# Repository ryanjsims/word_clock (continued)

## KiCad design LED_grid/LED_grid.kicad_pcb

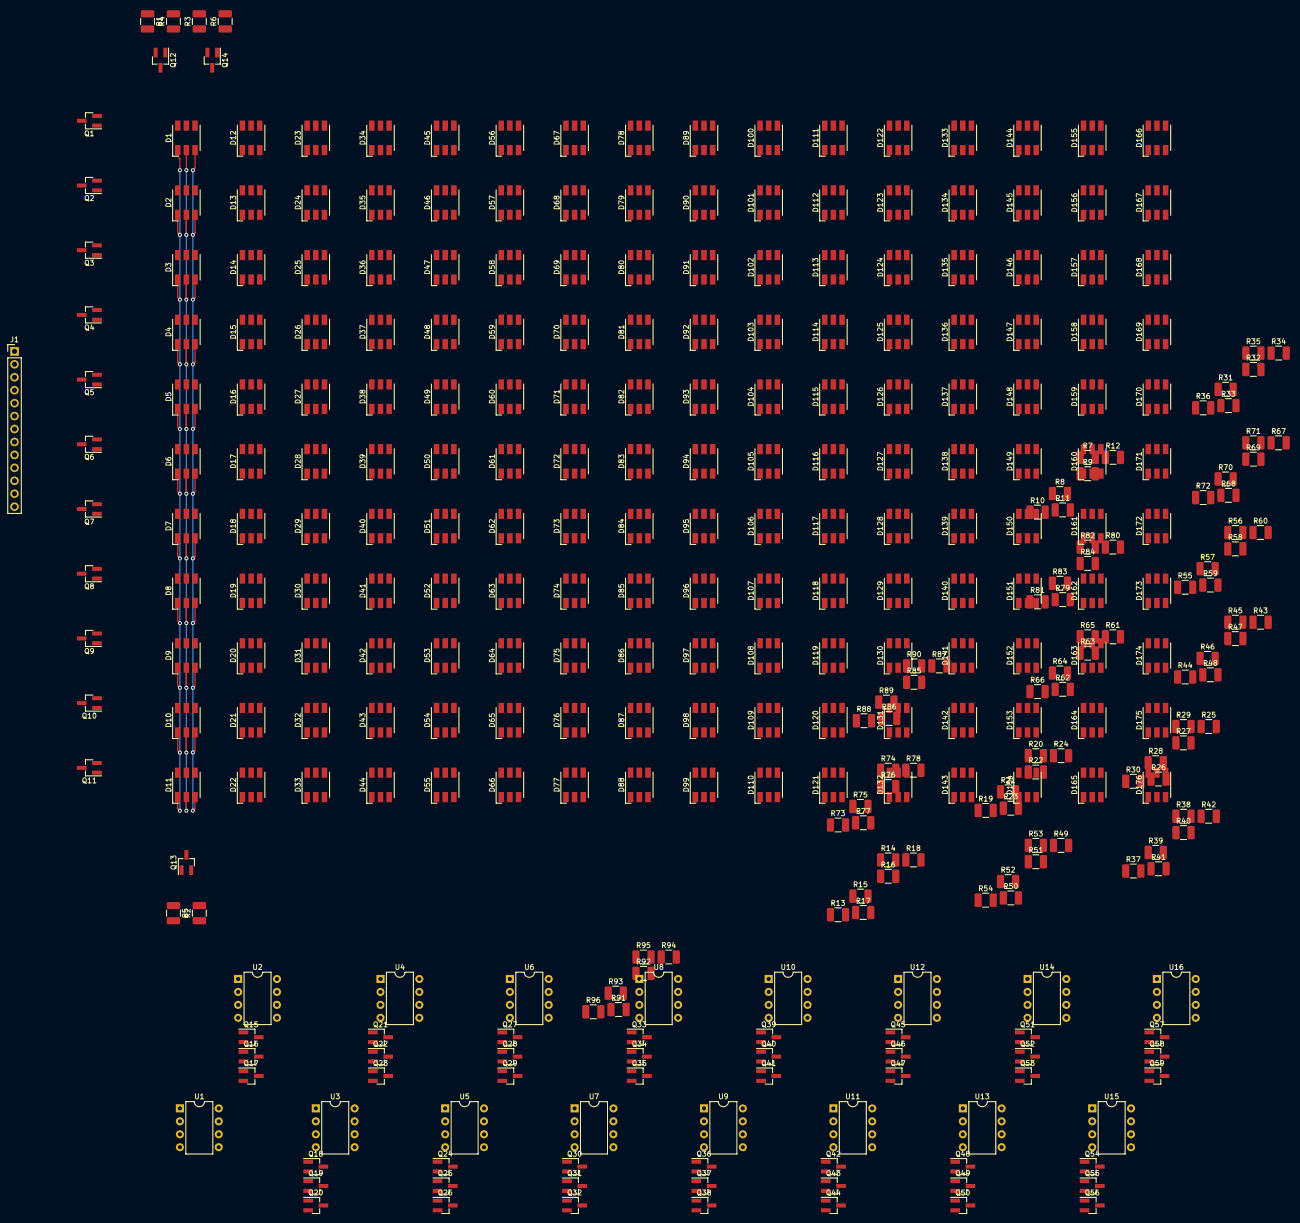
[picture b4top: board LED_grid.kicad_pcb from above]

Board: 2 copper layers, 348 parts (0 on the bottom side), 233 nets.

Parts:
D1, D2, D3, D4, D5, D6, D7, D8, D9, D10, D11, D12, D13, D14, D15, D16, D17, D18, D19, D20, D21, D22, D23, D24, D25, D26, D27, D28, D29, D30, D31, D32, D33, D34, D35, D36, D37, D38, D39, D40, D41, D42, D43, D44, D45, D46, D47, D48, D49, D50, D51, D52, D53, D54, D55, D56, D57, D58, D59, D60, D61, D62, D63, D64, D65, D66, D67, D68, D69, D70, D71, D72, D73, D74, D75, D76, D77, D78, D79, D80, D81, D82, D83, D84, D85, D86, D87, D88, D89, D90, D91, D92, D93, D94, D95, D96, D97, D98, D99, D100, D101, D102, D103, D104, D105, D106, D107, D108, D109, D110, D111, D112, D113, D114, D115, D116, D117, D118, D119, D120, D121, D122, D123, D124, D125, D126, D127, D128, D129, D130, D131, D132, D133, D134, D135, D136, D137, D138, D139, D140, D141, D142, D143, D144, D145, D146, D147, D148, D149, D150, D151, D152, D153, D154, D155, D156, D157, D158, D159, D160, D161, D162, D163, D164, D165, D166, D167, D168, D169, D170, D171, D172, D173, D174, D175, D176: LED_RGB; LED_RGB_5050-6
J1: Conn_01x13; PinHeader_1x13_P2.54mm_Vertical
Q1, Q2, Q3, Q4, Q5, Q6, Q7, Q8, Q9, Q10, Q11: FMMT620CT-ND; SOT-23_Handsoldering
Q12, Q13, Q14, Q15, Q16, Q17, Q18, Q19, Q20, Q21, Q22, Q23, Q24, Q25, Q26, Q27, Q28, Q29, Q30, Q31, Q32, Q33, Q34, Q35, Q36, Q37, Q38, Q39, Q40, Q41, Q42, Q43, Q44, Q45, Q46, Q47, Q48, Q49, Q50, Q51, Q52, Q53, Q54, Q55, Q56, Q57, Q58, Q59: 2N3904; SOT-23_Handsoldering
R1, R2, R3, R7, R8, R9, R13, R14, R15, R19, R20, R21, R25, R26, R27, R31, R32, R33, R37, R38, R39, R43, R44, R45, R49, R50, R51, R55, R56, R57, R61, R62, R63, R67, R68, R69, R73, R74, R75, R79, R80, R81, R85, R86, R87, R91, R92, R93: 10k; R_1210_3225Metric_Pad1.42x2.65mm_HandSolder
R4, R10, R16, R22, R28, R34, R40, R46, R52, R58, R64, R70, R76, R82, R88, R94: 100; R_1210_3225Metric_Pad1.42x2.65mm_HandSolder
R5, R6, R11, R12, R17, R18, R23, R24, R29, R30, R35, R36, R41, R42, R47, R48, R53, R54, R59, R60, R65, R66, R71, R72, R77, R78, R83, R84, R89, R90, R95, R96: 150; R_1210_3225Metric_Pad1.42x2.65mm_HandSolder
U1, U2, U3, U4, U5, U6, U7, U8, U9, U10, U11, U12, U13, U14, U15, U16: ATtiny85-20PU; DIP-8_W7.62mm

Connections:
+5V: Q1.2, Q2.2, Q3.2, Q4.2, Q5.2, Q6.2, Q7.2, Q8.2, Q9.2, Q10.2, Q11.2, U1.8, U2.8, U3.8, U4.8, U5.8, U6.8, U7.8, U8.8, U9.8, U10.8, U11.8, U12.8, U13.8, U14.8, U15.8, U16.8
/0: D1.4, D1.5, D1.6, D12.4, D12.5, D12.6, D23.4, D23.5, D23.6, D34.4, D34.5, D34.6, D45.4, D45.5, D45.6, D56.4, D56.5, D56.6, D67.4, D67.5, D67.6, D78.4, D78.5, D78.6, D89.4, D89.5, D89.6, D100.4, D100.5, D100.6, D111.4, D111.5, D111.6, D122.4, D122.5, D122.6, D133.4, D133.5, D133.6, D144.4, D144.5, D144.6, D155.4, D155.5, D155.6, D166.4, D166.5, D166.6, Q1.1
/1: D2.4, D2.5, D2.6, D13.4, D13.5, D13.6, D24.4, D24.5, D24.6, D35.4, D35.5, D35.6, D46.4, D46.5, D46.6, D57.4, D57.5, D57.6, D68.4, D68.5, D68.6, D79.4, D79.5, D79.6, D90.4, D90.5, D90.6, D101.4, D101.5, D101.6, D112.4, D112.5, D112.6, D123.4, D123.5, D123.6, D134.4, D134.5, D134.6, D145.4, D145.5, D145.6, D156.4, D156.5, D156.6, D167.4, D167.5, D167.6, Q2.1
/2: D3.4, D3.5, D3.6, D14.4, D14.5, D14.6, D25.4, D25.5, D25.6, D36.4, D36.5, D36.6, D47.4, D47.5, D47.6, D58.4, D58.5, D58.6, D69.4, D69.5, D69.6, D80.4, D80.5, D80.6, D91.4, D91.5, D91.6, D102.4, D102.5, D102.6, D113.4, D113.5, D113.6, D124.4, D124.5, D124.6, D135.4, D135.5, D135.6, D146.4, D146.5, D146.6, D157.4, D157.5, D157.6, D168.4, D168.5, D168.6, Q3.1
/3: D4.4, D4.5, D4.6, D15.4, D15.5, D15.6, D26.4, D26.5, D26.6, D37.4, D37.5, D37.6, D48.4, D48.5, D48.6, D59.4, D59.5, D59.6, D70.4, D70.5, D70.6, D81.4, D81.5, D81.6, D92.4, D92.5, D92.6, D103.4, D103.5, D103.6, D114.4, D114.5, D114.6, D125.4, D125.5, D125.6, D136.4, D136.5, D136.6, D147.4, D147.5, D147.6, D158.4, D158.5, D158.6, D169.4, D169.5, D169.6, Q4.1
/4: D5.4, D5.5, D5.6, D16.4, D16.5, D16.6, D27.4, D27.5, D27.6, D38.4, D38.5, D38.6, D49.4, D49.5, D49.6, D60.4, D60.5, D60.6, D71.4, D71.5, D71.6, D82.4, D82.5, D82.6, D93.4, D93.5, D93.6, D104.4, D104.5, D104.6, D115.4, D115.5, D115.6, D126.4, D126.5, D126.6, D137.4, D137.5, D137.6, D148.4, D148.5, D148.6, D159.4, D159.5, D159.6, D170.4, D170.5, D170.6, Q5.1
/5: D6.4, D6.5, D6.6, D17.4, D17.5, D17.6, D28.4, D28.5, D28.6, D39.4, D39.5, D39.6, D50.4, D50.5, D50.6, D61.4, D61.5, D61.6, D72.4, D72.5, D72.6, D83.4, D83.5, D83.6, D94.4, D94.5, D94.6, D105.4, D105.5, D105.6, D116.4, D116.5, D116.6, D127.4, D127.5, D127.6, D138.4, D138.5, D138.6, D149.4, D149.5, D149.6, D160.4, D160.5, D160.6, D171.4, D171.5, D171.6, Q6.1
/6: D7.4, D7.5, D7.6, D18.4, D18.5, D18.6, D29.4, D29.5, D29.6, D40.4, D40.5, D40.6, D51.4, D51.5, D51.6, D62.4, D62.5, D62.6, D73.4, D73.5, D73.6, D84.4, D84.5, D84.6, D95.4, D95.5, D95.6, D106.4, D106.5, D106.6, D117.4, D117.5, D117.6, D128.4, D128.5, D128.6, D139.4, D139.5, D139.6, D150.4, D150.5, D150.6, D161.4, D161.5, D161.6, D172.4, D172.5, D172.6, Q7.1
/7: D8.4, D8.5, D8.6, D19.4, D19.5, D19.6, D30.4, D30.5, D30.6, D41.4, D41.5, D41.6, D52.4, D52.5, D52.6, D63.4, D63.5, D63.6, D74.4, D74.5, D74.6, D85.4, D85.5, D85.6, D96.4, D96.5, D96.6, D107.4, D107.5, D107.6, D118.4, D118.5, D118.6, D129.4, D129.5, D129.6, D140.4, D140.5, D140.6, D151.4, D151.5, D151.6, D162.4, D162.5, D162.6, D173.4, D173.5, D173.6, Q8.1
/8: D9.4, D9.5, D9.6, D20.4, D20.5, D20.6, D31.4, D31.5, D31.6, D42.4, D42.5, D42.6, D53.4, D53.5, D53.6, D64.4, D64.5, D64.6, D75.4, D75.5, D75.6, D86.4, D86.5, D86.6, D97.4, D97.5, D97.6, D108.4, D108.5, D108.6, D119.4, D119.5, D119.6, D130.4, D130.5, D130.6, D141.4, D141.5, D141.6, D152.4, D152.5, D152.6, D163.4, D163.5, D163.6, D174.4, D174.5, D174.6, Q9.1
/9: D10.4, D10.5, D10.6, D21.4, D21.5, D21.6, D32.4, D32.5, D32.6, D43.4, D43.5, D43.6, D54.4, D54.5, D54.6, D65.4, D65.5, D65.6, D76.4, D76.5, D76.6, D87.4, D87.5, D87.6, D98.4, D98.5, D98.6, D109.4, D109.5, D109.6, D120.4, D120.5, D120.6, D131.4, D131.5, D131.6, D142.4, D142.5, D142.6, D153.4, D153.5, D153.6, D164.4, D164.5, D164.6, D175.4, D175.5, D175.6, Q10.1
/10: D11.4, D11.5, D11.6, D22.4, D22.5, D22.6, D33.4, D33.5, D33.6, D44.4, D44.5, D44.6, D55.4, D55.5, D55.6, D66.4, D66.5, D66.6, D77.4, D77.5, D77.6, D88.4, D88.5, D88.6, D99.4, D99.5, D99.6, D110.4, D110.5, D110.6, D121.4, D121.5, D121.6, D132.4, D132.5, D132.6, D143.4, D143.5, D143.6, D154.4, D154.5, D154.6, D165.4, D165.5, D165.6, D176.4, D176.5, D176.6, Q11.1
/B0: D1.3, D2.3, D3.3, D4.3, D5.3, D6.3, D7.3, D8.3, D9.3, D10.3, D11.3, Q14.3
/B1: D12.3, D13.3, D14.3, D15.3, D16.3, D17.3, D18.3, D19.3, D20.3, D21.3, D22.3, Q17.3
/B2: D23.3, D24.3, D25.3, D26.3, D27.3, D28.3, D29.3, D30.3, D31.3, D32.3, D33.3, Q20.3
/B3: D34.3, D35.3, D36.3, D37.3, D38.3, D39.3, D40.3, D41.3, D42.3, D43.3, D44.3, Q23.3
/B4: D45.3, D46.3, D47.3, D48.3, D49.3, D50.3, D51.3, D52.3, D53.3, D54.3, D55.3, Q26.3
/B5: D56.3, D57.3, D58.3, D59.3, D60.3, D61.3, D62.3, D63.3, D64.3, D65.3, D66.3, Q29.3
/B6: D67.3, D68.3, D69.3, D70.3, D71.3, D72.3, D73.3, D74.3, D75.3, D76.3, D77.3, Q32.3
/B7: D78.3, D79.3, D80.3, D81.3, D82.3, D83.3, D84.3, D85.3, D86.3, D87.3, D88.3, Q35.3
/B8: D89.3, D90.3, D91.3, D92.3, D93.3, D94.3, D95.3, D96.3, D97.3, D98.3, D99.3, Q38.3
/B9: D100.3, D101.3, D102.3, D103.3, D104.3, D105.3, D106.3, D107.3, D108.3, D109.3, D110.3, Q41.3
/B10: D111.3, D112.3, D113.3, D114.3, D115.3, D116.3, D117.3, D118.3, D119.3, D120.3, D121.3, Q44.3
/B11: D122.3, D123.3, D124.3, D125.3, D126.3, D127.3, D128.3, D129.3, D130.3, D131.3, D132.3, Q47.3
/B12: D133.3, D134.3, D135.3, D136.3, D137.3, D138.3, D139.3, D140.3, D141.3, D142.3, D143.3, Q50.3
/B13: D144.3, D145.3, D146.3, D147.3, D148.3, D149.3, D150.3, D151.3, D152.3, D153.3, D154.3, Q53.3
/B14: D155.3, D156.3, D157.3, D158.3, D159.3, D160.3, D161.3, D162.3, D163.3, D164.3, D165.3, Q56.3
/B15: D166.3, D167.3, D168.3, D169.3, D170.3, D171.3, D172.3, D173.3, D174.3, D175.3, D176.3, Q59.3
/D7_OUT: U8.7, U9.2
/DCLK: J1.13, U1.1, U2.1, U3.1, U4.1, U5.1, U6.1, U7.1, U8.1, U9.1, U10.1, U11.1, U12.1, U13.1, U14.1, U15.1, U16.1
/DIN: J1.12, U1.2
/G0: D1.2, D2.2, D3.2, D4.2, D5.2, D6.2, D7.2, D8.2, D9.2, D10.2, D11.2, Q13.3
/G1: D12.2, D13.2, D14.2, D15.2, D16.2, D17.2, D18.2, D19.2, D20.2, D21.2, D22.2, Q16.3
/G2: D23.2, D24.2, D25.2, D26.2, D27.2, D28.2, D29.2, D30.2, D31.2, D32.2, D33.2, Q19.3
/G3: D34.2, D35.2, D36.2, D37.2, D38.2, D39.2, D40.2, D41.2, D42.2, D43.2, D44.2, Q22.3
/G4: D45.2, D46.2, D47.2, D48.2, D49.2, D50.2, D51.2, D52.2, D53.2, D54.2, D55.2, Q25.3
/G5: D56.2, D57.2, D58.2, D59.2, D60.2, D61.2, D62.2, D63.2, D64.2, D65.2, D66.2, Q28.3
/G6: D67.2, D68.2, D69.2, D70.2, D71.2, D72.2, D73.2, D74.2, D75.2, D76.2, D77.2, Q31.3
/G7: D78.2, D79.2, D80.2, D81.2, D82.2, D83.2, D84.2, D85.2, D86.2, D87.2, D88.2, Q34.3
/G8: D89.2, D90.2, D91.2, D92.2, D93.2, D94.2, D95.2, D96.2, D97.2, D98.2, D99.2, Q37.3
/G9: D100.2, D101.2, D102.2, D103.2, D104.2, D105.2, D106.2, D107.2, D108.2, D109.2, D110.2, Q40.3
/G10: D111.2, D112.2, D113.2, D114.2, D115.2, D116.2, D117.2, D118.2, D119.2, D120.2, D121.2, Q43.3
/G11: D122.2, D123.2, D124.2, D125.2, D126.2, D127.2, D128.2, D129.2, D130.2, D131.2, D132.2, Q46.3
/G12: D133.2, D134.2, D135.2, D136.2, D137.2, D138.2, D139.2, D140.2, D141.2, D142.2, D143.2, Q49.3
/G13: D144.2, D145.2, D146.2, D147.2, D148.2, D149.2, D150.2, D151.2, D152.2, D153.2, D154.2, Q52.3
/G14: D155.2, D156.2, D157.2, D158.2, D159.2, D160.2, D161.2, D162.2, D163.2, D164.2, D165.2, Q55.3
/G15: D166.2, D167.2, D168.2, D169.2, D170.2, D171.2, D172.2, D173.2, D174.2, D175.2, D176.2, Q58.3
/PWM Controller/B_PWM: R3.1, U1.3
/PWM Controller/G_PWM: R2.1, U1.6
/PWM Controller/R_PWM: R1.1, U1.5
/R0: D1.1, D2.1, D3.1, D4.1, D5.1, D6.1, D7.1, D8.1, D9.1, D10.1, D11.1, Q12.3
/R1: D12.1, D13.1, D14.1, D15.1, D16.1, D17.1, D18.1, D19.1, D20.1, D21.1, D22.1, Q15.3
/R2: D23.1, D24.1, D25.1, D26.1, D27.1, D28.1, D29.1, D30.1, D31.1, D32.1, D33.1, Q18.3
/R3: D34.1, D35.1, D36.1, D37.1, D38.1, D39.1, D40.1, D41.1, D42.1, D43.1, D44.1, Q21.3
/R4: D45.1, D46.1, D47.1, D48.1, D49.1, D50.1, D51.1, D52.1, D53.1, D54.1, D55.1, Q24.3
/R5: D56.1, D57.1, D58.1, D59.1, D60.1, D61.1, D62.1, D63.1, D64.1, D65.1, D66.1, Q27.3
/R6: D67.1, D68.1, D69.1, D70.1, D71.1, D72.1, D73.1, D74.1, D75.1, D76.1, D77.1, Q30.3
/R7: D78.1, D79.1, D80.1, D81.1, D82.1, D83.1, D84.1, D85.1, D86.1, D87.1, D88.1, Q33.3
/R8: D89.1, D90.1, D91.1, D92.1, D93.1, D94.1, D95.1, D96.1, D97.1, D98.1, D99.1, Q36.3
/R9: D100.1, D101.1, D102.1, D103.1, D104.1, D105.1, D106.1, D107.1, D108.1, D109.1, D110.1, Q39.3
/R10: D111.1, D112.1, D113.1, D114.1, D115.1, D116.1, D117.1, D118.1, D119.1, D120.1, D121.1, Q42.3
/R11: D122.1, D123.1, D124.1, D125.1, D126.1, D127.1, D128.1, D129.1, D130.1, D131.1, D132.1, Q45.3
/R12: D133.1, D134.1, D135.1, D136.1, D137.1, D138.1, D139.1, D140.1, D141.1, D142.1, D143.1, Q48.3
/R13: D144.1, D145.1, D146.1, D147.1, D148.1, D149.1, D150.1, D151.1, D152.1, D153.1, D154.1, Q51.3
/R14: D155.1, D156.1, D157.1, D158.1, D159.1, D160.1, D161.1, D162.1, D163.1, D164.1, D165.1, Q54.3
/R15: D166.1, D167.1, D168.1, D169.1, D170.1, D171.1, D172.1, D173.1, D174.1, D175.1, D176.1, Q57.3
/ROW0: J1.1, Q1.3
/ROW1: J1.2, Q2.3
/ROW2: J1.3, Q3.3
/ROW3: J1.4, Q4.3
/ROW4: J1.5, Q5.3
/ROW5: J1.6, Q6.3
/ROW6: J1.7, Q7.3
/ROW7: J1.8, Q8.3
/ROW8: J1.9, Q9.3
/ROW9: J1.10, Q10.3
/ROW10: J1.11, Q11.3
/sheet5C02A49B/B_PWM: R39.1, U7.3
/sheet5C02A49B/DIN: U6.7, U7.2
/sheet5C02A49B/G_PWM: R38.1, U7.6
/sheet5C02A49B/R_PWM: R37.1, U7.5
/sheet5C02A49D/B_PWM: R45.1, U8.3
/sheet5C02A49D/DIN: U7.7, U8.2
/sheet5C02A49D/G_PWM: R44.1, U8.6
/sheet5C02A49D/R_PWM: R43.1, U8.5
/sheet5C02A497/B_PWM: R27.1, U5.3
/sheet5C02A497/DIN: U4.7, U5.2
/sheet5C02A497/G_PWM: R26.1, U5.6
/sheet5C02A497/R_PWM: R25.1, U5.5
/sheet5C02A499/B_PWM: R33.1, U6.3
/sheet5C02A499/DIN: U5.7, U6.2
/sheet5C02A499/G_PWM: R32.1, U6.6
/sheet5C02A499/R_PWM: R31.1, U6.5
/sheet5C02E5C7/B_PWM: R51.1, U9.3
/sheet5C02E5C7/G_PWM: R50.1, U9.6
/sheet5C02E5C7/R_PWM: R49.1, U9.5
/sheet5C02E5C9/B_PWM: R57.1, U10.3
/sheet5C02E5C9/DIN: U9.7, U10.2
/sheet5C02E5C9/G_PWM: R56.1, U10.6
/sheet5C02E5C9/R_PWM: R55.1, U10.5
/sheet5C02E5CB/B_PWM: R63.1, U11.3
/sheet5C02E5CB/DIN: U10.7, U11.2
/sheet5C02E5CB/G_PWM: R62.1, U11.6
/sheet5C02E5CB/R_PWM: R61.1, U11.5
/sheet5C7E23D8/B_PWM: R75.1, U13.3
/sheet5C7E23D8/DIN: U12.7, U13.2
/sheet5C7E23D8/G_PWM: R74.1, U13.6
/sheet5C7E23D8/R_PWM: R73.1, U13.5
/sheet5C7E23D9/B_PWM: R81.1, U14.3
/sheet5C7E23D9/DIN: U13.7, U14.2
/sheet5C7E23D9/G_PWM: R80.1, U14.6
/sheet5C7E23D9/R_PWM: R79.1, U14.5
/sheet5C026B32/B_PWM: R9.1, U2.3
/sheet5C026B32/DIN: U1.7, U2.2
/sheet5C026B32/G_PWM: R8.1, U2.6
/sheet5C026B32/R_PWM: R7.1, U2.5
/sheet5C87E357/B_PWM: R93.1, U16.3
/sheet5C87E357/DIN: U15.7, U16.2
/sheet5C87E357/G_PWM: R92.1, U16.6
/sheet5C87E357/R_PWM: R91.1, U16.5
/sheet5C156C5A/B_PWM: R69.1, U12.3
/sheet5C156C5A/DIN: U11.7, U12.2
/sheet5C156C5A/G_PWM: R68.1, U12.6
/sheet5C156C5A/R_PWM: R67.1, U12.5
/sheet5C853AF2/B_PWM: R87.1, U15.3
/sheet5C853AF2/DIN: U14.7, U15.2
/sheet5C853AF2/G_PWM: R86.1, U15.6
/sheet5C853AF2/R_PWM: R85.1, U15.5
/sheet5C02892F/B_PWM: R15.1, U3.3
/sheet5C02892F/DIN: U2.7, U3.2
/sheet5C02892F/G_PWM: R14.1, U3.6
/sheet5C02892F/R_PWM: R13.1, U3.5
/sheet5C028931/B_PWM: R21.1, U4.3
/sheet5C028931/DIN: U3.7, U4.2
/sheet5C028931/G_PWM: R20.1, U4.6
/sheet5C028931/R_PWM: R19.1, U4.5
GND: R4.2, R5.2, R6.2, R10.2, R11.2, R12.2, R16.2, R17.2, R18.2, R22.2, R23.2, R24.2, R28.2, R29.2, R30.2, R34.2, R35.2, R36.2, R40.2, R41.2, R42.2, R46.2, R47.2, R48.2, R52.2, R53.2, R54.2, R58.2, R59.2, R60.2, R64.2, R65.2, R66.2, R70.2, R71.2, R72.2, R76.2, R77.2, R78.2, R82.2, R83.2, R84.2, R88.2, R89.2, R90.2, R94.2, R95.2, R96.2, U1.4, U2.4, U3.4, U4.4, U5.4, U6.4, U7.4, U8.4, U9.4, U10.4, U11.4, U12.4, U13.4, U14.4, U15.4, U16.4
unnamed: Q12.1, R4.1
unnamed: Q12.2, R1.2
unnamed: Q13.1, R5.1
unnamed: Q13.2, R2.2
unnamed: Q14.1, R6.1
unnamed: Q14.2, R3.2
unnamed: Q15.1, R10.1
unnamed: Q15.2, R7.2
unnamed: Q16.1, R11.1
unnamed: Q16.2, R8.2
unnamed: Q17.1, R12.1
unnamed: Q17.2, R9.2
unnamed: Q18.1, R16.1
unnamed: Q18.2, R13.2
unnamed: Q19.1, R17.1
unnamed: Q19.2, R14.2
unnamed: Q20.1, R18.1
unnamed: Q20.2, R15.2
unnamed: Q21.1, R22.1
unnamed: Q21.2, R19.2
unnamed: Q22.1, R23.1
unnamed: Q22.2, R20.2
unnamed: Q23.1, R24.1
unnamed: Q23.2, R21.2
unnamed: Q24.1, R28.1
unnamed: Q24.2, R25.2
unnamed: Q25.1, R29.1
unnamed: Q25.2, R26.2
unnamed: Q26.1, R30.1
unnamed: Q26.2, R27.2
unnamed: Q27.1, R34.1
unnamed: Q27.2, R31.2
unnamed: Q28.1, R35.1
unnamed: Q28.2, R32.2
unnamed: Q29.1, R36.1
unnamed: Q29.2, R33.2
unnamed: Q30.1, R40.1
unnamed: Q30.2, R37.2
unnamed: Q31.1, R41.1
unnamed: Q31.2, R38.2
unnamed: Q32.1, R42.1
unnamed: Q32.2, R39.2
unnamed: Q33.1, R46.1
unnamed: Q33.2, R43.2
unnamed: Q34.1, R47.1
unnamed: Q34.2, R44.2
unnamed: Q35.1, R48.1
unnamed: Q35.2, R45.2
unnamed: Q36.1, R52.1
unnamed: Q36.2, R49.2
unnamed: Q37.1, R53.1
unnamed: Q37.2, R50.2
unnamed: Q38.1, R54.1
unnamed: Q38.2, R51.2
unnamed: Q39.1, R58.1
unnamed: Q39.2, R55.2
unnamed: Q40.1, R59.1
unnamed: Q40.2, R56.2
unnamed: Q41.1, R60.1
unnamed: Q41.2, R57.2
unnamed: Q42.1, R64.1
unnamed: Q42.2, R61.2
unnamed: Q43.1, R65.1
unnamed: Q43.2, R62.2
unnamed: Q44.1, R66.1
unnamed: Q44.2, R63.2
unnamed: Q45.1, R70.1
unnamed: Q45.2, R67.2
unnamed: Q46.1, R71.1
unnamed: Q46.2, R68.2
unnamed: Q47.1, R72.1
unnamed: Q47.2, R69.2
unnamed: Q48.1, R76.1
unnamed: Q48.2, R73.2
unnamed: Q49.1, R77.1
unnamed: Q49.2, R74.2
unnamed: Q50.1, R78.1
unnamed: Q50.2, R75.2
unnamed: Q51.1, R82.1
unnamed: Q51.2, R79.2
unnamed: Q52.1, R83.1
unnamed: Q52.2, R80.2
unnamed: Q53.1, R84.1
unnamed: Q53.2, R81.2
unnamed: Q54.1, R88.1
unnamed: Q54.2, R85.2
unnamed: Q55.1, R89.1
unnamed: Q55.2, R86.2
unnamed: Q56.1, R90.1
unnamed: Q56.2, R87.2
unnamed: Q57.1, R94.1
unnamed: Q57.2, R91.2
unnamed: Q58.1, R95.1
unnamed: Q58.2, R92.2
unnamed: Q59.1, R96.1
unnamed: Q59.2, R93.2

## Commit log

2018-09-06 Added to git
2018-10-16 Added all files
2018-10-16 Added everything for real
2018-11-28 Added LED grid kicad files
2018-12-05 Added additional led grid without controllers
2018-12-05 Added led grid controllers files
2018-12-05 Added extra columns to grid along with 5V pin to connectors
2018-12-21 Added 3 updated designs and partslist for revision 1 and 2 of the led grid
